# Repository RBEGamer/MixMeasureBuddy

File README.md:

# MixMeasureBuddy

MixMeasureBuddy's smart cocktail scale revolutionizes home bartending by offering accurate ingredient measurements and a vast library of cocktail recipes personalized to your liquor collection. Enjoy the art of mixology with ease and precision.

Discover the advanced features that set MixMeasureBuddy apart from traditional kitchen scales.

## FEATURES

Discover the advanced features that set MixMeasureBuddy apart from traditional kitchen scales:

* **Open-Source** MixMeasureBuddy is 100% open-source and can be build using a few simple and cheap parts.
* **Connectivity Features** Enjoy seamless integration with a companion webapp for sharing personalized cocktail recipes with other MixMeasureBuddy owners.
* **Offline Usage** Recipes are stored offline and locally on the MixMeasureBerry and can be edited using a text editor
* **User-Friendly Interface** Easily navigate the scale's intuitive interface for effortless cocktail making.
* **Customizable Recipes** Access a plethora of cocktail recipes tailored to your liquor cabinet for endless mixing possibilities.
* **Precision Measurements** Eliminate the guesswork and achieve consistent results with exact ingredient measurements every time.

## BOM

### 3D PRINTED PARTS

**Please read the 3d printing instructions before printing any part!**

* 1x `ring.stl`
* 1x `breadboard_mount.stl`
* 1x `inner_cellplate.stl`
* 1x `hinge.stl`
* 1x `bottom.stl`
* 1x `display_clamp.stl`
* 1x `display_mount.stl`
* 1x `encoder_clamp.stl`

#### CELLPLATE

* 1x `cellplate_<style>.stl`

The top plate exists in three different styles:

* `normal` - plain top plate
* `ring` - with an 82-84mm diameter ring depression in the center to plate a rubber band in it
* `plate` - with an 80mm diameter circular depression to place a rubber sheet in it

The `ring` and `plate` variants offer better grip of the glasses while standing on the platic top plate.

#### BOTTOM PLATE

If a `8mm` wide led strip is used please set the scale of `bottom.stl` to `120%` in **Z** direction.

#### 3D PRINT SETTINGS

* Layer height: `0.2` - `0.4`mm
* Support: `Support on buildplate only`
* Inflill: `20%`

### MECHANICAL

* 6x `Heat Inserts M3`
* 6x `M3x10 BHCS`
* 4x `M4x10 BHCS` - depends on load cell screw threads
* 3x `Heat Inserts M4`
* 3x `M4x10 BHCS`
* 8x `Cylindrical Magnet D5mm H8mm` or four additional `Heat Inserts M4` + four additional `M4x10 SHCS` to replace the magnets

### MISC

* `Super Glue` - to glue magnets into `inner_cellplate` and `cellplate`

### ELECTRICAL

* 1x `Raspberry Pi Pico` or `Raspberry Pi Pico W`
* 1x `LOAD CELL` with dimensions of `60x12x12mm` and at least `2kg`, for example `YZC-131`
* 1x `HX711`
* 1x `1.3" I2C OLED SSH1306`
* 1x `Encoder` e.g. `KY-040`
* 50cm `WS2812` strip
* Jumperwires  >12x `male-male`, >10x `male-female`
* 1x Breadboard with dimensions of `83 x 55mm`, for example `Mini Breadboard 400 Pin`
* [OPTIONAL] `SPI SD TF Karte Memory Card Shield Modul`
* [OPTIONAL] `Battery Expansion Shield 18650 V3`

### TOOLS

* `Soldering Iron`
* `Hotglue`

## HARDWARE BUILD

### SCHEMATIC

The following diagram shows the internal wiring of the individual components of the `MixMeasureBuddy`.
Only the `Raspberry Pi Pico`, button and the `HX711` are placed on the small breadboard.
The display, `LEDs` and the encoder(-module) are connected with longer cables so that they can be attached to the 3D printed parts at the intended mounting locations.

The circuit diagram was created in the Fritzing software. The project can be found under `documenation/schematic/`.
After the function of all parts has been tested, the connections on the breadboard should be fixed with hot glue so that they do not come loose during transportation.

### NOTES

To fix accuracy issues on several `HX711` boards, two addional resistors are needed.
Please refer to this guide: [HX711 – Auswahl und Beschaltung](https://beelogger.de/sensoren/waegezellen_hx711/hx711_beschaltung/#:~:text=HX711%20Modul%20Auswahl,Wägezelle%20und%20einen%20einstellbaren%20Messbrückenverstärker.)

#### [OPTIONAL] SD CARD READER

It is possible to connect an additional SD card reader. This makes it possible to save the recipes on an SD card.  
Please connect the SD card reader to the following pins on the `Raspberry Pi Pico`:

| Raspberry Pi Pico GPIO | SD CARD MODULE GPIO |
|------------------------|---------------------|
| VCC (Pin 36)           | 3V3 (OUT) / VCC     |
| GND (Pin 18)           | GND                 |
| GP10                   | SCK                 |
| GP8                    | MISO                |
| GP11                   | MOSI                |
| GP9                    | CS                  |

No further software changes are needed later on. The systems firmware detects the connected SD card automatically.

#### [OPTIONAL] BATTERY EXPANSION

The `Battery Expansion Shield 18650 V3` can be mounted on the `breadboard_mount.stl` later on.
In oder to connect the `Battery Expansion` to the `Raspberry Pi Pico GPIO` please follow the wiring table below:

| Raspberry Pi Pico GPIO | Battery Expansion |
|------------------------|-------------------|
| VBUS (Pin 40)          | 5V OUT            |
| GND  (Pin 38)          | GND               |

## SOFTWARE INSTALLATION

Please check the `Releases` page of this repository for prebuild firmware archives.

To initially flash the software to the `Raspberry Pi Pico`, the `BOOT` button must first be held down when plugging in the `USB` cable.
A new removable disk will then appear on the `PC`. The `firmware.uf2` is then copied to this.
The microcontroller will then restart and the MixMeasureBuddy logo should appear on the display.

If you want to build the software yourself from source or add modifications, please refer to the `SOFTWARE DEVELOPMENT` chapter.

**NOTE** There is an firmware archive with older stable versions located in `src/firmware/build/archive`.

### SOFTWARE UPGRADE

If a old version of the firmwre was already installed on the `Raspberry Pi Pico`, please flash the [flash_nuke.uf2](https://github.com/dwelch67/raspberrypi-pico/blob/main/flash_nuke.uf2) first! This clears all user settings!

**NOTE** Please backup all your stored recipes first!

## MECHANICAL BUILD

### 1. DISPLAY MOUNT

* 1x `Heat Inserts M3`
* 1x `M3x10`
* 1x `1.3" I2C OLED SSH1306`
* 4x Jumperwires `male-female`
* 1x `display_clamp.stl`
* 1x `display_mount.stl`

#### INSTRUCTIONS

1. Insert the `M3 Heat Insert` using a soldering iron into `display_mount`
2. Place the `1.3" I2C OLED SSH1306` display inside `display_mount` 
3. Press the display into place using the `display_clamp` and one `M3x10`
4. Connect four `male-female` jumperwires onto the display header
5. Glue the jumperwire ends and the header together using a drop of hotgleue
6. [OPTIONAL] Lock down the jumperwires using a small zip-tie

### 2. ENCODER MOUNT

* 2x `Heat Inserts M3`
* 1x `M3x10`
* 4x Jumperwires `male-female`
* 1x `Encoder` e.g. `KY-040`
* 1x `encoder_clamp.stl`
* 1x `ring.stl`

#### INSTRUCTIONS

1. Connect five `male-female` jumperwires onto the encoder pcb header
2. Insert the two `M3 Heat Inserts` using a soldering iron into `ring` part
3. Insert the encoder pcb into `ring` shell
4. Use the `encoder_clamp` and one `M3x10` to press the encoder into the `ring`

### 3. ASSEMBLE DISPLAY AND RING PARTS

* 1x `M3x10`
* 1x `hinge.stl`

#### INSTRUCTIONS

* Place the display assembly in the indentation
* Use the `hinge` and  one `M3x10` to press the assembly into the `ring`

### 3. LOADCELL

* 4x `M4x10` - depends on load cell screw threads
* 4x `Cylindrical Magnet D5mm H8mm`
* 1x `LOAD CELL`

* 1x `inner_cellplate.stl`

#### INSTRUCTIONS

1. Insert the three `M4 Heat Inserts` using a soldering iron into `ring` part
2. Screw the loadcell using two `M4x10` screws into the `ring`
3. Use the remaining `M4x10` screws to mount the `inner_cellplate` on the load cell arm, in the center of the `ring` cutout
4. Glue four magnets into `inner_cellplate`

**NOTE** The cables from the load cell are facing towards the shell of the `ring`

### 4. BREADBOARD

* 4x `Heat Inserts M3`
* 4x `M3x10 BHCS`
* 1x `ASSEMBLED BREADBOARD`
* 1x `breadboard_mount.stl`

#### INSTRUCTIONS

1. Insert the four `M3 Heat Inserts` using a soldering iron into `breadboard_mount` part
2. [OPTIONAL] Screw the `Battery Expansion Shield 18650 V3` into the side using two `M3x10`
3. Remove the protective film from the breadboard bottom side and place it ontop `breadboard_mount`stl`
4. Use the remaining two `M3x10` screws to fix `breadboard_mount` and `ring` together into place

**NOTE** Please connect all remaining components (`Encoder`, `Display`, ...) to the breadboard. See chapter `SCHEMATIC` again.
**NOTE** Its a good time to test the electronics again! Please refer to the `SOFTWARE INSTALLATION` chapter.

### 5. BOTTOM

* `WS2812` strip
* 3x `M4x10 SHCS`
* 3x  Jumperwire `male-male`
* 1x `bottom.stl`

#### INSTRUCTIONS

1. Solder three `male-male` jumperwires onto the `WS2812` strip (`VCC`, `GND`, `DIN`)
2. Remove the protective film from the `WS2812` strip and place them on the center ring of the `bottom`
3. Screw the `bottom` using the three `M4x10` screws onto `ring` assembly.

**NOTE** Make sure that the `Micro USB` is going thought opening between `bottom`  and `ring`.
**NOTE** If no `Battery Expansion Shield 18650 V3` is installed, please insert a `Micro USB` cable into the `Raspberry Pi Pico` before attaching the `bottom`.

### 6. CELLPLATE

* 4x `Cylindrical Magnet D5mm H8mm` or 4x `M4x6.x mm` heat inserts + 4x `M4x10 SHCS` to replace the magnets
* 1x `cellplate.stl`

#### INSTRUCTIONS

##### USING MAGNETS
1. Glue four magnets into `cellplate`
2. Place the `cellplate` on the `inner_cellplate`

**NOTE** Please ensure that the magnets in the two parts `cellplate`, `inner_cellplate` attract each other on opposite sides

##### USING HEAT INSERTS

1. Insert the `heatinserts` in the four holes of the `cellplate`
2. 
3. Place the `cellplate` on the `inner_cellplate`
4. Align the flat edge of the `cellplate` with the display and use the four `M4x10 SHCS` screws to connect the `cellplate` with `inner_cellplate`

# USAGE

Once the hardware has been set up and the software has been flashed to the microcontroller, the system can be set up for the first time.
The basic operation and calibration of the system is described below.

## MENU NAVIGATION

After switching on the power supply, e.g. via a power bank, the main menu appears on the display immediately after the logo screen.
Navigation in the system is very easy thanks to the rotary encoder. 
The right and left rotation of the encoder can be used to scroll through the separate menu entries.
If you want to enter / activate a menu item, simply press the button on the encoder.
To exit a menu/recipe, the encoder button must be held down for at least half a second.

## CALIBRATION

If the scales menu or a recipe is now called up. The weighing results can deviate significantly from reality.
This is due to the installation direction of the load cell, its mounting and other factors.
The menu item `CALIBRATION` is provided for this purpose.
For this process, the scale is measured with and without weight and the corresponding correction factors are determined.

A known weight with at least `50g` is therefore required. This can be a glass of water, for example, which has previously been measured with a kitchen scale.

After starting the calibration routine, the user is guided through the following steps one after the other:

* Measure empty scale
* User enters weight of calibration object
* User places calibration object on scale
* User removes calibration object if shown by display

**NOTE** If the scales light up red, please `DONT MOVE OR TOUCH`.

**NOTE** The `IKEA POKAL` glass has a weight of 390g (empty) :)

## RUN A RECIPE

## ADDING CUSTOM RECIPES

A recipe in the context of the MixMeasureBuddy consists of a JSON object in a .recipe file. This contains meta data such as the name and description of the recipe as well as a series of instructions that the user should execute to complete the recipe. The following instruction types can be used for this purpose:

* SCALE - Weigh until x grams reached
* WAIT - Wait x seconds
* CONFIRM - Confirm that it has been done.

There are two ways to create a new recipe manually:

### BY USING recipe.py CLASS

* Create a new empty folder
* Copy the `src/firmware/src/static_modules/recipe.py` into the new created folder
* Create a new `MyRecipe.py` file with the following content Python script below
* Change the name, description and steps according your imagination

```python
# SEE example_recipes.py FOR FURTHER / DETAILED EXAMPLES
import recipe

example_recipe: recipe.recipe = recipe.recipe("Tequila Sunrise", "A nice Tequila Sunrise Cocktail", "1.0.0", ["Tequila"])
# ADD A SCALE STEP: ADD x g TO THE GLASS
example_recipe.add_step(recipe.recipe_step.create_scale_step(_ingredient_name="White Tequila", _target_value = 10))
# ADD A SCALE STEP: ADD x g TO THE GLASS
example_recipe.add_step(recipe.create_scale_step(_ingredient_name="Orange Juice", _target_value = 120))
# ADD CONFIRM STEP: ADD ICE AND CONFIRM WITH A BUTTON PRESS
example_recipe.add_step(recipe.create_scale_step(_ingredient_name="Ice", _current_step_text="Add Ice"))
# ADD A SCALE STEP: ADD x g TO THE GLASS
example_recipe.add_step(recipe.create_scale_step(_ingredient_name="Grenadine", _target_value = 40))
# ADD A WAIT STEP:  WAIT x SECONDS
example_recipe.add_step(recipe.create_scale_step(_current_step_text="Wait for settle down", _target_value = 10))

# EXPORT THE RECIPES AS JSON BASE .RECIPE FILE
with open("MyRecipe.recipe, "w") as file:
  file.write(json.dumps(example_recipe.to_dict()))
# COPY OVER THE .RECIPE FILE TO THE SCALE
```

Run the 

```bash
$ python MyRecipe.py
$ cat MyRecipe.recipe
```

This scripts created a new `MyRecipe.recipe` file. The content is a `JSON` strucutre which is compatible with the recipe system of the scale.

### CREATEING A JSON BASED .recipe FILE

```json
{
    "filename": "Tequila_Sunrise.recipe",
    "name": "Tequila Sunrise",
    "steps": [{
        "text": "",
        "ingredient": "White Tequila",
        "amount": 10,
        "action": 0
    }, {
        "text": "",
        "ingredient": "Orange Juice",
        "amount": 120,
        "action": 0
    }, {
        "text": "Add Ice",
        "ingredient": "Ice",
        "amount": -1,
        "action": 1
    }, {
        "text": "",
        "ingredient": "Grenadine",
        "amount": 40,
        "action": 0
    }, {
        "text": "Wait for settle down",
        "ingredient": "",
        "amount": 10,
        "action": 2
    }],
    "description": "A nice Tequila Sunrise Cocktail",
    "version": "1.0.0"
}
```

### COPY RECIPES TO SCALE

To access the files and the Micropython environment on the scale directly, its possible to use these two example programs below:

* [Thonny](https://github.com/thonny/thonny/)
* [rshell](https://github.com/dhylands/rshell)

In this example, a previously created recipe file is to be copied to the `MixMeasureBuddy` so that it can be used.
After connecting the flashed `MixMeasureBuddy` to a host PC using a USB cable, run the following commands in order to transfer the `.recipe` file.

#### THONNY

For installation, please refer to the installation guid on the website [INSTALL_THONNY](https://thonny.org).

The image shows the steps in order to connect the `MixMeasureBuddy` and access its files:

1. Select the board
2. Connect to python repl running on the board
3. Use the file explorer to add/edit/remove files 

#### RSHELL

```bash
# INSTALL RSHELL
$ sudo pip3 install rshell

#TEST CONNECTION
$ rshell
# OR
$ rshell -p /dev/ttyUSB0
# COPY
$ rshell cp MyRecipe.recipe /data/MyRecipe.recipe
```

The recipe is now stored on the `MixMeasureBuddy`. Powercycle the device to load the new recipes!

### USER CONFIGURATION

If a `Raspberry Pi Pico W` is used, its possible to use the recipe editor and the recipe api update functions.
Here the wifi credentials needs to be set using the `SETTINGS.json` file on the scale.
Please use the same procedure described above to edit files on the scale filesystem.

# FIRMWARE DEVELOPMENT

The microcontroller firmware of the `Raspberry Pi Pico` was created in micropython and is automatically created with the pre-built image. 
The source code files are located in the folder `src/firmware_rp2040` and the Python source code files in the folder `src/firmware_rp2040/src`.
The program `Thonny` can be used to adapt the software directly on the scale.

## DIFFERENT HARDWARE CONFIG

The global hardware configuration (used display type, pin definitions and other settings) are stored in the `Config.py` loacted in the virtual filesystem.
Its possbile to modify this file using the `REPL` or` Thonny` as described above.

## STRUCTURE

The entry point of the software is in the `main.py`, which is called by the custom pre-boot script `boot.py`. The general configuration of the hardware (e.g. which pins the buttons are connected to) is done in the `config.py` file.

The control of the hardware components is done in the files:

* `ui.py` - UI system + display control
* `ledring.py` - LED effects for the LED ring
* `Scales.py` - readout of the HX711
* `settings.py`- filesystem access for writing/reading recipe files and settings

All these classes can be easily called from all other scripts using the singleton pattern. This makes integration very simple and uniform:

```python
import ledring
import ui
import Scale
# CLEAR DISPLAY
ui().clear()
# SET LED RING
ledring().set_neopixel_full_hsv(ledring().COLOR_PRESET_HSV_H__BLUE)
# GET CURRENT SCALE MEASUREMENT
ScaleInterface().get_current_weight()
```

The individual menus are designed as a plug-in system. This allows you to quickly create your own extensions.
The plugins are designated in the system with the prefix `menu_entry_*.py` and the functions are derived from the base class `menu_entry.py`.
This consists of an `activate`, `teardown` and `update` function, which are called accordingly when the corresponding menu entry is called.

```python
class menu_entry_MyPlugin(menu_entry.menu_entry):

    def __init__(self):
        super().__init__("MyPlugin", "My nice plugin")
    # WILL BE CALLED IF USER SELECTS PLUGIN
    def preview(self):
        print("preview {}".format(self.name))
        ui().show_recipe_information(self.name, self.description)
    
    # WILL BE CALLED IF USER ACTIVATES PLUGIN
    # E.G. DO SETUP STUFF
    def activate(self):
        print("activate {}".format(self.name))
        ui().show_titlescreen()

    # WILL BE CALLED IF USER EXISTS PLUGIN
    # E.G. DELETE RESOURCES
    def teardown(self):
        print("teardown {}".format(self.name))

    # WILL BE CALLED IF A USER PRESSES A BUTTON, EVERY SECOND OR IF THE WEIGHT ON LOAD CELL CHANGES
    def update(self, _system_command: system_command.system_command):
        
        if _system_command.type == system_command.system_command.COMMAND_TYPE_NAVIGATION:
            if _system_command.action == system_command.system_command.NAVIGATION_ENTER: #  OK BUTTON
                pass
            elif _system_command.action == system_command.system_command.NAVIGATION_LEFT: # NEXT BUTTON
                pass
            elif _system_command.action == system_command.system_command.NAVIGATION_RIGHT: # PREV BUTTON
                pass

        elif _system_command.type == system_command.system_command.COMMAND_TYPE_SCALE:
              print("CURRENT WEIGHT: {}".format(_system_command.value))
  
        elif _system_command.type == system_command.system_command.COMMAND_TYPE_TIMER_IRQ:
              print("ELAPSED TIME SINCE LAST CALL: {}".format(_system_command.value))
           
```

To add the plugin, import the module in `main.py` and add the class into the menu tree:

```python
from menu_entry_MyPlugin import menu_entry_MyPlugin
menu_manager.menu_manager().add_subentries(menu_entry_MyPlugin.menu_entry_MyPlugin())
```

Its also possible to add sub-menus using the `menu_entry_submenu` plugin:

```python
# CREATE SUBMENU WITH CUSTOM TITLE
submenu: menu_entry_submenu.menu_entry_submenu = menu_entry_submenu.menu_entry_submenu("SYSTEM", "ACCESS SYSTEM SETTINGS")
# ADD MENU ENTRIES TO THE SUBMENU
submenu.add_subentries(menu_entry_calibration.menu_entry_calibration())
submenu.add_subentries(menu_entry_calibration.menu_entry_calibration())
submenu.add_subentries(menu_entry_calibration.menu_entry_calibration())
# ADD THE SUBMENU TO THE MAIN MENU
menu_manager.menu_manager().add_subentries(submenu)
```

## FIRMWARE IMAGE

To create a finished and complete firmware image, the folder `src/firmware_rp2040` contains a bash script which creates the images using `Docker` for the `Raspberry Pi Pico` and `Raspberry Pi Pico W` and the required boot configurations.

```bash
# INSTALL AND RUN DOCKER https://docs.docker.com/engine/install/
$ cd src/firmware_rp2040
$ bash ./build_firmware_docker.sh
# RESULTS ARE LOCATED IN THE build FOLDER
```

## BUILD SYSTEM BACKGROUND

One problem was how to build and distribute the Micropython images automatically via e.g. GitHub.
The way documented by Micropython does not allow the user to change the code and data after building the u2f, because they are permanently written to the flash (static/lib) fodlers.
That's why the complicated build process was created using a Docker image that installs a pre application boot procedure, so that the user source code to the Python file system during the first boot.
This way, functions can be easily added/modified by the user and at the same time the finished software can be easily distributed.

# TODO

* Cocktail database webapp - `src/webapp`

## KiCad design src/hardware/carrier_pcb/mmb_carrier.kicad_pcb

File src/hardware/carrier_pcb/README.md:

# MixMeasureBuddy carrier PCB (Raspberry Pi Pico 2 W)

A 2-layer, 83 × 70 mm board that replaces the breadboard and jumper-wire nest. The top 83 × 55 mm is the breadboard-sized area; the bottom 15 mm band holds the optional LiPo section.

* **Raspberry Pi Pico 2 W**: socketed on 2 × 20 pin headers (or soldered directly), with USB at the board edge
* **HX711** load-cell ADC (v1.1): a ready-made HX711 module plugs into the J4 socket (the bare chip circuit of v1.0 was removed)
* **2 navigation buttons** (LEFT / RIGHT): 6 × 6 mm THT tactile switches on the board
* Headers for the **OLED**, **encoder**, **WS2812 ring**, **load cell**, optional **SD card** and optional **5 V battery shield**
* **Optional LiPo section**: charger, step-up converter, power switch header and battery-voltage sense
* **Stepper driver socket** (v1.1): a StepStick / Pololu-footprint socket (A4988, DRV8825, TMC2208/2209 modules) with a 4-pin motor header
* **USB-C PD motor supply** (v1.1): a second USB-C port with a CH224K PD trigger that asks the charger for **12 V** for the motor only

KiCad 10 project: `mmb_carrier/` (`.kicad_pro`, `.kicad_sch`, `.kicad_pcb`).
Status: ERC 0 violations, DRC 0 violations, 0 unconnected items, 0 schematic-parity issues.

| Top | Bottom |
|---|---|
|  |  |

## Pin mapping (matches `src/firmware/src/config.py`, so the firmware works unchanged)

| Function | Pico GPIO (pin) | Board connector |
|---|---|---|
| OLED SDA / SCL (I2C0) | GP16 (21) / GP17 (22) | J1: 1 GND, 2 VCC (3V3), 3 SCL, 4 SDA |
| Encoder CLK / DT / SW | GP20 (26) / GP19 (25) / GP18 (24) | J2: 1 CLK, 2 DT, 3 SW, 4 + (3V3), 5 GND, in KY-040 order |
| WS2812 data | GP28 (34), through 330 Ω R3 | J3: 1 +5V (VSYS), 2 DIN, 3 GND |
| Button LEFT / RIGHT | GP3 (5) / GP2 (4), switch to GND (internal pull-up) | SW1 / SW2 |
| HX711 module SCK / DT | GP4 (6) / GP5 (7) | J4 socket: 1 GND, 2 DT, 3 SCK, 4 VCC (3V3) |
| Load cell | n/a | soldered to the HX711 module: E+ red, E- black, A- white, A+ green |
| SD card (SPI1, optional) | GP8 MISO, GP9 CS, GP10 SCK, GP11 MOSI | J5: 1 GND, 2 3V3, 3 MISO, 4 MOSI, 5 SCK, 6 CS |
| 5 V in (battery shield, optional) | VBUS (40) | J6: 1 +5V, 2 GND |
| LiPo cell (optional) | n/a | J7 JST-PH 2.0: 1 = **+**, 2 = − |
| Power switch (optional) | n/a | J8: external on/off switch, or a jumper for always-on |
| Battery voltage (optional) | GP26 / ADC0 (31) = VBAT / 2 | n/a |
| Stepper STEP / DIR | GP6 (9) / GP7 (10) | A1 StepStick socket |
| Stepper EN (active low) | GP1 (2), 10k pull-up R13 = driver off at boot | A1 StepStick socket |
| Stepper motor | n/a | J10: 1 = 1B, 2 = 1A (coil 1), 3 = 2A, 4 = 2B (coil 2); silk shows 2B 2A 1A 1B from left to right |
| Motor supply 12 V | n/a | J9 USB-C (power only), PD charger required |

## Optional LiPo section (bottom band)

Leave every part in the band unpopulated if you don't need a battery; the rest of the board works the same without it.

* **Charger, U3 (MCP73831-2-OT):** charges a single 3.7 V LiPo from USB at 500 mA (R4 = 2 kΩ; use 4.7 kΩ for about 200 mA with small cells). The red CHG LED is on while the cell is charging.
* **Load sharing (Q2 AO3401A + D1):** with USB plugged in, the step-up runs from USB and the battery only charges. Without USB, Q2 connects the battery.
* **Power switch, J8:** sits in series with the step-up input. Wire a slide switch from the enclosure to it, or fit a jumper. The battery still charges while the switch is off.
* **Step-up, U4 (MT3608):** makes 5.1 V with a 10 µH inductor and R7/R8 = 75k/10k. D3 feeds that into VSYS, the Pico's recommended way to add a second power source. The WS2812 header now runs from VSYS, so the ring works on battery too. The MT3608 handles roughly 0.8–1 A out of a LiPo, which is plenty for the 26 LEDs at the firmware's brightness limit.
* **Battery level:** R9/R10 (220k/220k) put VBAT/2 on GP26. The current firmware doesn't read it yet; in MicroPython, `machine.ADC(26).read_u16() * 3.3 / 65535 * 2` gives the battery voltage.
* **⚠ Check polarity:** JST-PH LiPo leads are not standardized. Before plugging in a cell, make sure its red wire lands on pin 1 (marked **+**).

## Stepper driver and 12 V USB-C PD supply (v1.1)

* **Driver socket, A1:** two 1 × 8 female 2.54 mm headers, 12.7 mm (0.5") apart, for any StepStick-pinout module. The silkscreen inside the socket marks **GND / DIR** at the top (Pico side) and **VMOT / EN** at the bottom. The square pad is GND. Check the orientation before plugging in a module: a reversed driver is destroyed as soon as power is applied.
* **Logic:** VDD = 3V3, so STEP / DIR / EN use 3.3 V logic. EN has a 10k pull-up (R13), so the motor stays de-energised until the firmware drives GP1 low. RESET and SLEEP are tied together and pulled high (R14).
* **Microstepping:** JP1 / JP2 / JP3 (labelled MS1 / MS2 / MS3) are open solder jumpers. Open = low, bridged = 3V3. The resulting mode depends on the module (A4988 / DRV8825: all open = full step; TMC2209: MS1 = MS2 = low = 1/8 step). On some TMC220x modules the MS3 / RESET positions carry PDN/UART instead, so check the module's pinout.
* **Motor supply, J9 + U5 (CH224K):** a USB-C power-only receptacle feeds **VMOT only**; the Pico, LEDs and HX711 keep running from the Pico's own USB (or the LiPo section). CH224K negotiates 12 V with R12 = 24k (6.8k = 9 V, 56k = 15 V). It is PD only: DP/DM are shorted on the chip side and not wired to the receptacle. VDD is fed from VBUS through R11 (1k) with C12 (1 µF).
* **Bulk capacitance:** C14 100 µF / 25 V low-ESR electrolytic plus C13 100 nF, next to the VMOT pin. If you change R12 to 15 V, keep the 25 V cap. For 20 V (R12 not fitted) use a 35 V part.
* **Charger requirement:** the charger must offer a 12 V PD profile (check its label). Some chargers only offer 5/9/15/20 V, and with those VMOT stays at 5 V. A4988 / DRV8825 drivers stay in under-voltage lockout at 5 V, while TMC2209 modules run (weakly) from 5 V.
* **Layout:** the whole motor power loop (USB-C, bulk cap, driver, motor header) sits in the left half of the board, far from the HX711 module socket J4 on the right edge. VMOT is routed at 0.8 mm and the motor phases at 0.6 mm, both without vias.
* **Moved for v1.1:** SW1 / SW2 (LEFT / RIGHT) moved to the right of the driver socket, and the SD header J5 moved 2.54 mm to the right. Nets and pin mapping are unchanged.
* **Firmware:** not changed yet; the pins above (GP6 STEP, GP7 DIR, GP1 EN) are free in `config.py`.

## HX711 module (v1.1)

* **J4** is a 1 × 4 female 2.54 mm socket on the right board edge. A ready-made HX711 module (the common green or red board) plugs in with its 4-pin header. The pin order is **GND, DT, SCK, VCC**, as printed on most modules and next to J4 on the silkscreen. If your module uses a different order, wire it to the labels instead of plugging it in directly.
* The module is powered from **3V3**, so DT and SCK use 3.3 V logic and are safe for the RP2350. The area next to J4 (where the v1.0 HX711 chip sat) is free of parts, so the module can lie flat there on right-angle pins, or stand upright in the socket.
* Solder the load cell to the module's E+ / E- / A- / A+ pads (red, black, white, green on most cells).
* GP4 (SCK) and GP5 (DT) are the same pins as before, so the firmware works unchanged. The bare-chip circuit (U2, Q1, R1, R2, C1-C6) and the old load-cell header are gone.
* Many cheap modules need the accuracy fix described in the main README's HX711 note (the linked beelogger guide). Apply it on the module itself.
* After swapping the excitation source (module instead of the v1.0 on-board circuit), run the calibration menu once.

## Layout notes

* The Pico W/2 W antenna keepout from the footprint is respected: no copper or tracks under the antenna end.
* Both layers have a GND pour with stitching vias on a 5 mm grid.
* Four M3 mounting holes sit at 4 mm from each corner.
* Reference designators in the LiPo band and in the USB-C PD / stepper area (except A1 and J10) are on the fab layer only (no space for silkscreen); see the schematic or the pick-and-place file.
* Signal tracks are 0.25 mm, supply tracks 0.4–0.5 mm, VMOT 0.8 mm and motor phases 0.6 mm, with 0.2 mm clearance and 0.6/0.3 mm vias. Any standard 2-layer fab can make this.

## Fabrication files (`mmb_carrier/fab/`)

* `mmb_carrier_gerbers.zip`: Gerbers and Excellon drill file
* `mmb_carrier_bom.csv`: BOM with an `LCSC` column (plus 2 × 1×20 female 2.54 mm headers if you socket the Pico, and 2 × 1×8 female 2.54 mm headers for the A1 stepper socket)
* `mmb_carrier_pos.csv`: pick-and-place file for the SMD parts (KiCad format)
* `mmb_carrier_jlcpcb_bom.csv` + `mmb_carrier_jlcpcb_cpl.csv`: BOM (`Comment, Designator, Footprint, LCSC`) and placement file (`Designator, Mid X, Mid Y, Layer, Rotation`) for JLCPCB SMT assembly of the 30 SMD parts

### LCSC part numbers

Every orderable part carries an `LCSC` field in the schematic and on the PCB footprint. The numbers were checked against the LCSC / JLCPCB part pages (November 2026); check stock before ordering.

| Part | LCSC | Notes |
|---|---|---|
| 0805 resistors 330 / 1k / 2k / 10k / 24k / 75k / 100k / 220k | C17630 / C17513 / C17604 / C17414 / C17575 / C17819 / C149504 / C17556 | UNI-ROYAL 0805W8F series, 1 %; 75k is an extended part |
| 100 nF 0805 / 1 µF 0805 / 4.7 µF 0805 / 22 µF 1206 | C49678 / C28323 / C1779 / C12891 | X7R 50 V, X7R 50 V, X5R 25 V, X5R 25 V |
| C14 100 µF 25 V, 6.3 × 5.8 mm | C178540 | Panasonic EEE-FK1E101SP |
| SS14 / red 0805 LED / AO3401A | C2480 / C84256 / C15127 | |
| MCP73831T-2ACI/OT / MT3608 / CH224K | C424093 / C84817 / C970725 | extended parts |
| L1 Bourns SRN6045TA-100M | C2046332 | second source on the same footprint: SXN SMNR6045-100MT, C135304 |
| J9 GCT USB4125-GF-A (USB-C, power only) | C3151650 | exact part for the footprint |
| J4 1×4 female header / A1 1×8 female header (2 pcs) | C2718488 / C27438 | 8.5 mm high |
| J7 JST S2B-PH-K-S / SW1, SW2 6 × 6 × 5 mm tact switch | C173752 / C393938 | |
| Male pin headers J1-J3, J5, J6, J8, J10 | C2337 | 1×40 breakable, cut to length (no field on the symbols) |

The JLCPCB files cover the SMD parts only; the through-hole parts (headers, switches, JST, Pico) are hand-soldered. Rotations in the CPL are KiCad's: check the part orientation in JLCPCB's placement preview before confirming, especially for the SOT-23 parts, the diodes, the electrolytic C14, U5 and J9.
* `../mmb_carrier_schematic.pdf`: schematic

## Regenerating

The board is generated from `tools/design.py`, which holds the parts, pins and nets. To rebuild:

```bash
tools/build.sh
```

The script writes the schematic, runs ERC, places parts, routes the board with the bundled grid router (`tools/gen_pcb.py`), pours GND, runs DRC with schematic parity, and exports the fab outputs. If you edit the board by hand in KiCad, stop using the script for that board, because the next run overwrites it.

**Note for v1.1:** the stepper / USB-C PD rework was added directly to the KiCad files, not to `tools/design.py`. Running the old generator would remove it.

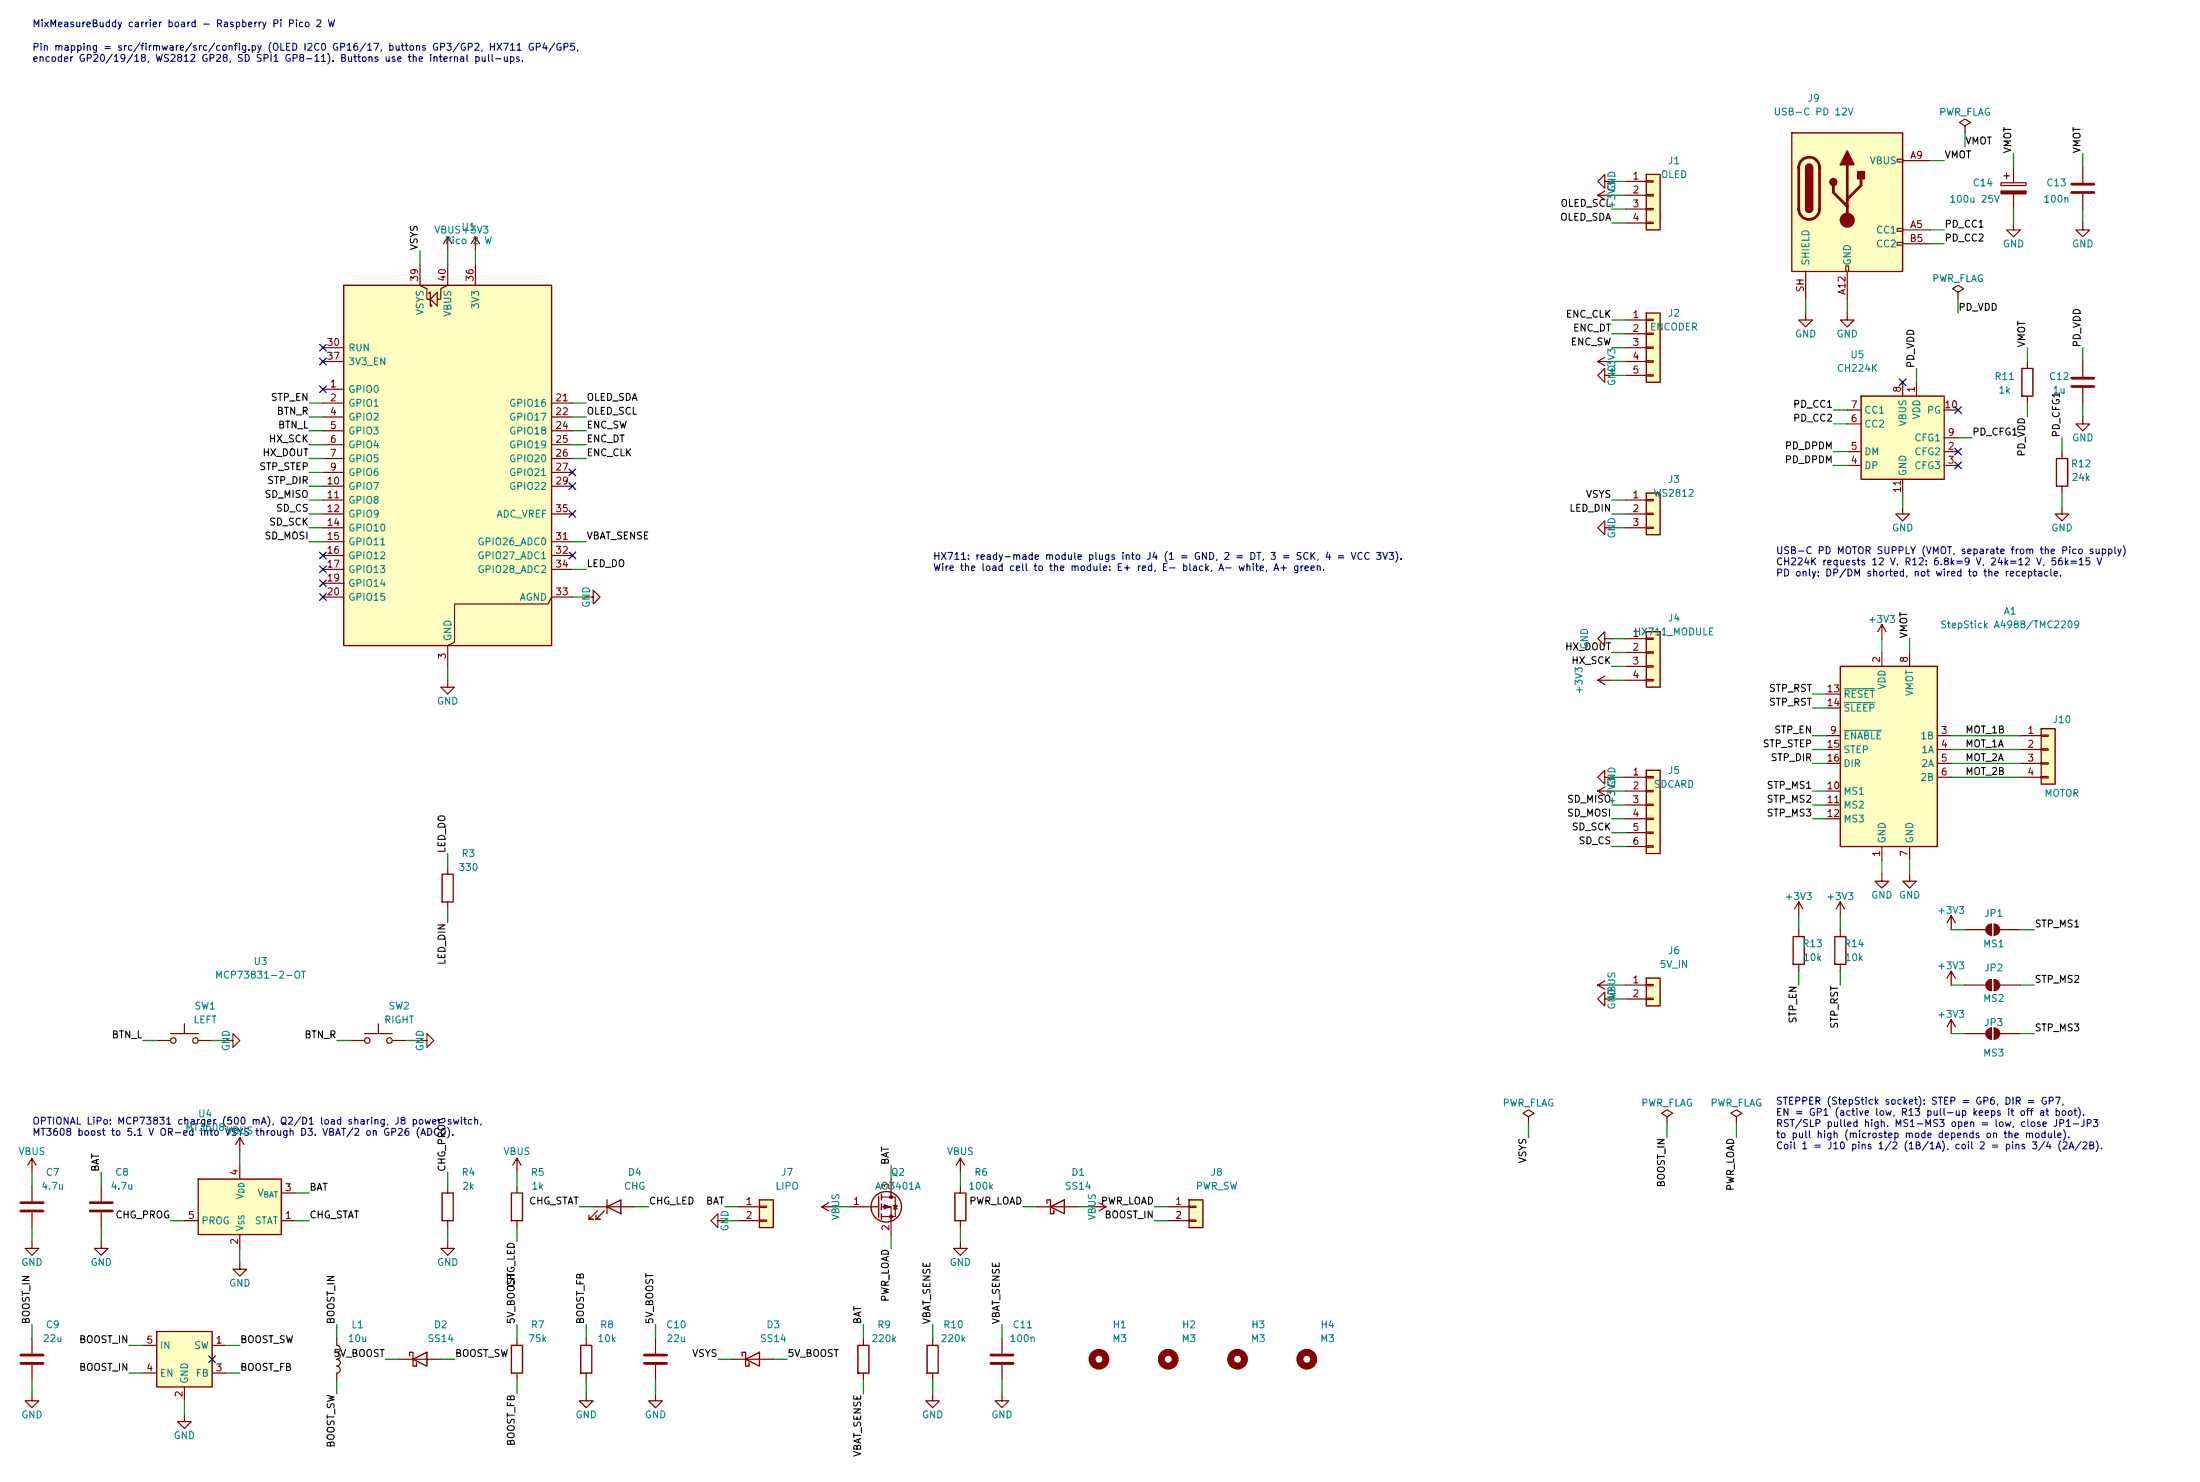
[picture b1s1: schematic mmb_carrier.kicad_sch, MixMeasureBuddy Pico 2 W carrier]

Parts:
A1: StepStick A4988/TMC2209; Pololu_Breakout-16_15.2x20.3mm; LCSC C27438
C7, C8: 4.7u; C_0805_2012Metric; LCSC C1779
C9, C10: 22u; C_1206_3216Metric; LCSC C12891
C11, C13: 100n; C_0805_2012Metric; LCSC C49678
C12: 1u; C_0805_2012Metric; LCSC C28323
C14: 100u 25V; CP_Elec_6.3x5.8; LCSC C178540
D1, D2, D3: SS14; D_SMA; LCSC C2480
D4: CHG; LED_0805_2012Metric; LCSC C84256
H1, H2, H3, H4: M3; MountingHole_3.2mm_M3
J1: OLED; PinHeader_1x04_P2.54mm_Vertical
J2: ENCODER; PinHeader_1x05_P2.54mm_Vertical
J3: WS2812; PinHeader_1x03_P2.54mm_Vertical
J4: HX711_MODULE; PinSocket_1x04_P2.54mm_Vertical; LCSC C2718488
J5: SDCARD; PinHeader_1x06_P2.54mm_Vertical
J6: 5V_IN; PinHeader_1x02_P2.54mm_Vertical
J7: LIPO; JST_PH_S2B-PH-K_1x02_P2.00mm_Horizontal; LCSC C173752
J8: PWR_SW; PinHeader_1x02_P2.54mm_Vertical
J9: USB-C PD 12V; USB_C_Receptacle_GCT_USB4125-xx-x_6P_TopMnt_Horizontal; LCSC C3151650
J10: MOTOR; PinHeader_1x04_P2.54mm_Vertical
JP1: MS1; SolderJumper-2_P1.3mm_Open_RoundedPad1.0x1.5mm
JP2: MS2; SolderJumper-2_P1.3mm_Open_RoundedPad1.0x1.5mm
JP3: MS3; SolderJumper-2_P1.3mm_Open_RoundedPad1.0x1.5mm
L1: 10u; L_Bourns_SRN6045TA; LCSC C2046332
Q2: AO3401A; SOT-23; LCSC C15127
R3: 330; R_0805_2012Metric; LCSC C17630
R4: 2k; R_0805_2012Metric; LCSC C17604
R5, R11: 1k; R_0805_2012Metric; LCSC C17513
R6: 100k; R_0805_2012Metric; LCSC C149504
R7: 75k; R_0805_2012Metric; LCSC C17819
R8, R13, R14: 10k; R_0805_2012Metric; LCSC C17414
R9, R10: 220k; R_0805_2012Metric; LCSC C17556
R12: 24k; R_0805_2012Metric; LCSC C17575
SW1: LEFT; SW_PUSH_6mm; LCSC C393938
SW2: RIGHT; SW_PUSH_6mm; LCSC C393938
U1: Pico 2 W; RaspberryPi_Pico_Common_THT
U3: MCP73831-2-OT; SOT-23-5; LCSC C424093
U4: MT3608; SOT-23-6; LCSC C84817
U5: CH224K; SSOP-10-1EP_3.9x4.9mm_P1mm_EP2.1x3.3mm; LCSC C970725

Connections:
+3V3: A1.2 (VDD), J1.2, J2.4, J4.4, J5.2, JP1.1 (A), JP2.1 (A), JP3.1 (A), R13.1, R14.1, U1.36 (3V3)
/5V_BOOST: C10.1, D2.1 (K), D3.2 (A), R7.1
/BAT: C8.1, J7.1, Q2.3 (D), R9.1, U3.3 (V_{BAT})
/BOOST_FB: R7.2, R8.1, U4.3 (FB)
/BOOST_IN: C9.1, J8.2, L1.1, U4.4 (EN), U4.5 (IN)
/BOOST_SW: D2.2 (A), L1.2, U4.1 (SW)
/BTN_L: SW1.1, U1.5 (GPIO3)
/BTN_R: SW2.1, U1.4 (GPIO2)
/CHG_LED: D4.2 (A), R5.2
/CHG_PROG: R4.1, U3.5 (PROG)
/CHG_STAT: D4.1 (K), U3.1 (STAT)
/ENC_CLK: J2.1, U1.26 (GPIO20)
/ENC_DT: J2.2, U1.25 (GPIO19)
/ENC_SW: J2.3, U1.24 (GPIO18)
/HX_DOUT: J4.2, U1.7 (GPIO5)
/HX_SCK: J4.3, U1.6 (GPIO4)
/LED_DIN: J3.2, R3.2
/LED_DO: R3.1, U1.34 (GPIO28_ADC2)
/MOT_1A: A1.4 (1A), J10.2
/MOT_1B: A1.3 (1B), J10.1
/MOT_2A: A1.5 (2A), J10.3
/MOT_2B: A1.6 (2B), J10.4
/OLED_SCL: J1.3, U1.22 (GPIO17)
/OLED_SDA: J1.4, U1.21 (GPIO16)
/PD_CC1: J9.A5 (CC1), U5.7 (CC1)
/PD_CC2: J9.B5 (CC2), U5.6 (CC2)
/PD_CFG1: R12.1, U5.9 (CFG1)
/PD_DPDM: U5.4 (DP), U5.5 (DM)
/PD_VDD: C12.1, R11.2, U5.1 (VDD)
/PWR_LOAD: D1.1 (K), J8.1, Q2.2 (S)
/SD_CS: J5.6, U1.12 (GPIO9)
/SD_MISO: J5.3, U1.11 (GPIO8)
/SD_MOSI: J5.4, U1.15 (GPIO11)
/SD_SCK: J5.5, U1.14 (GPIO10)
/STP_DIR: A1.16 (DIR), U1.10 (GPIO7)
/STP_EN: A1.9 (~ENABLE), R13.2, U1.2 (GPIO1)
/STP_MS1: A1.10 (MS1), JP1.2 (B)
/STP_MS2: A1.11 (MS2), JP2.2 (B)
/STP_MS3: A1.12 (MS3), JP3.2 (B)
/STP_RST: A1.13 (~RESET), A1.14 (~SLEEP), R14.2
/STP_STEP: A1.15 (STEP), U1.9 (GPIO6)
/VBAT_SENSE: C11.1, R9.2, R10.1, U1.31 (GPIO26_ADC0)
/VMOT: A1.8 (VMOT), C13.1, C14.1, J9.A9 (VBUS), J9.B9 (VBUS), R11.1
/VSYS: D3.1 (K), J3.1, U1.39 (VSYS)
GND: A1.1 (GND), A1.7 (GND), C7.2, C8.2, C9.2, C10.2, C11.2, C12.2, C13.2, C14.2, J1.1, J2.5, J3.3, J4.1, J5.1, J6.2, J7.2, J9.A12 (GND), J9.B12 (GND), J9.SH (SHIELD), R4.2, R6.2, R8.2, R10.2, R12.2, SW1.2, SW2.2, U1.3 (GND), U1.8 (GND), U1.13 (GND), U1.18 (GND), U1.23 (GND), U1.28 (GND), U1.33 (AGND), U1.38 (GND), U3.2 (V_{SS}), U4.2 (GND), U5.11 (GND)
VBUS: C7.1, D1.2 (A), J6.1, Q2.1 (G), R5.1, R6.1, U1.40 (VBUS), U3.4 (V_{DD})

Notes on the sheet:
MixMeasureBuddy carrier board - Raspberry Pi Pico 2 W
Pin mapping = src/firmware/src/config.py (OLED I2C0 GP16/17, buttons GP3/GP2, HX711 GP4/GP5, encoder GP20/19/18, WS2812 GP28, SD SPI1 GP8-11). Buttons use the internal pull-ups.
OPTIONAL LiPo: MCP73831 charger (500 mA), Q2/D1 load sharing, J8 power switch, MT3608 boost to 5.1 V OR-ed into VSYS through D3. VBAT/2 on GP26 (ADC0).
USB-C PD MOTOR SUPPLY (VMOT, separate from the Pico supply) CH224K requests 12 V. R12: 6.8k=9 V, 24k=12 V, 56k=15 V PD only: DP/DM shorted, not wired to the receptacle.
STEPPER (StepStick socket): STEP = GP6, DIR = GP7, EN = GP1 (active low, R13 pull-up keeps it off at boot). RST/SLP pulled high. MS1-MS3 open = low, close JP1-JP3 to pull high (microstep mode depends on the module). Coil 1 = J10 pins 1/2 (1B/1A), coil 2 = pins 3/4 (2A/2B).
HX711: ready-made module plugs into J4 (1 = GND, 2 = DT, 3 = SCK, 4 = VCC 3V3). Wire the load cell to the module: E+ red, E- black, A- white, A+ green.

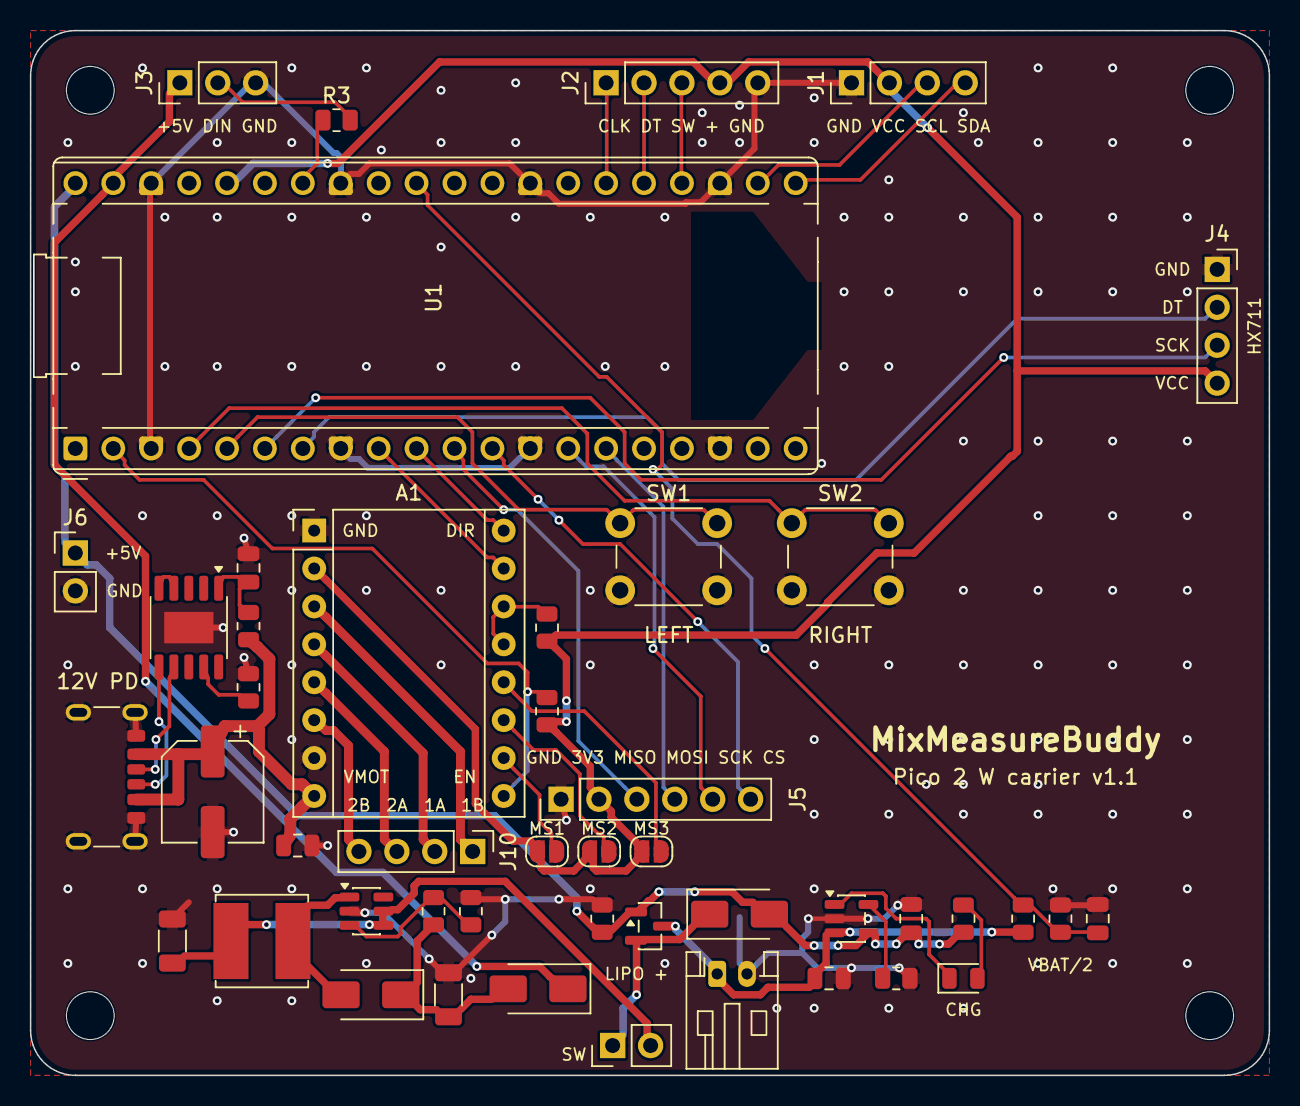
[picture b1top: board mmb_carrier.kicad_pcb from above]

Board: 2 copper layers, 83.0 x 70.0 mm, 50 parts (0 on the bottom side), 46 nets.

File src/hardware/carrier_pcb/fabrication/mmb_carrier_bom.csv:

"Reference","Value","Footprint","LCSC","QUANTITY"
"A1","StepStick A4988/TMC2209","Module:Pololu_Breakout-16_15.2x20.3mm","C27438","1"
"C7,C8","4.7u","Capacitor_SMD:C_0805_2012Metric","C1779","2"
"C9,C10","22u","Capacitor_SMD:C_1206_3216Metric","C12891","2"
"C11,C13","100n","Capacitor_SMD:C_0805_2012Metric","C49678","2"
"C12","1u","Capacitor_SMD:C_0805_2012Metric","C28323","1"
"C14","100u 25V","Capacitor_SMD:CP_Elec_6.3x5.8","C178540","1"
"D1-D3","SS14","Diode_SMD:D_SMA","C2480","3"
"D4","CHG","LED_SMD:LED_0805_2012Metric","C84256","1"
"J1","OLED","Connector_PinHeader_2.54mm:PinHeader_1x04_P2.54mm_Vertical","","1"
"J2","ENCODER","Connector_PinHeader_2.54mm:PinHeader_1x05_P2.54mm_Vertical","","1"
"J3","WS2812","Connector_PinHeader_2.54mm:PinHeader_1x03_P2.54mm_Vertical","","1"
"J4","HX711_MODULE","Connector_PinSocket_2.54mm:PinSocket_1x04_P2.54mm_Vertical","C2718488","1"
"J5","SDCARD","Connector_PinHeader_2.54mm:PinHeader_1x06_P2.54mm_Vertical","","1"
"J6","5V_IN","Connector_PinHeader_2.54mm:PinHeader_1x02_P2.54mm_Vertical","","1"
"J7","LIPO","Connector_JST:JST_PH_S2B-PH-K_1x02_P2.00mm_Horizontal","C173752","1"
"J8","PWR_SW","Connector_PinHeader_2.54mm:PinHeader_1x02_P2.54mm_Vertical","","1"
"J9","USB-C PD 12V","Connector_USB:USB_C_Receptacle_GCT_USB4125-xx-x_6P_TopMnt_Horizontal","C3151650","1"
"J10","MOTOR","Connector_PinHeader_2.54mm:PinHeader_1x04_P2.54mm_Vertical","","1"
"L1","10u","Inductor_SMD:L_Bourns_SRN6045TA","C2046332","1"
"Q2","AO3401A","Package_TO_SOT_SMD:SOT-23","C15127","1"
"R3","330","Resistor_SMD:R_0805_2012Metric","C17630","1"
"R4","2k","Resistor_SMD:R_0805_2012Metric","C17604","1"
"R5,R11","1k","Resistor_SMD:R_0805_2012Metric","C17513","2"
"R6","100k","Resistor_SMD:R_0805_2012Metric","C149504","1"
"R7","75k","Resistor_SMD:R_0805_2012Metric","C17819","1"
"R8,R13,R14","10k","Resistor_SMD:R_0805_2012Metric","C17414","3"
"R9,R10","220k","Resistor_SMD:R_0805_2012Metric","C17556","2"
"R12","24k","Resistor_SMD:R_0805_2012Metric","C17575","1"
"SW1","LEFT","Button_Switch_THT:SW_PUSH_6mm","C393938","1"
"SW2","RIGHT","Button_Switch_THT:SW_PUSH_6mm","C393938","1"
"U1","Pico 2 W","Module:RaspberryPi_Pico_Common_THT","","1"
"U3","MCP73831-2-OT","Package_TO_SOT_SMD:SOT-23-5","C424093","1"
"U4","MT3608","Package_TO_SOT_SMD:SOT-23-6","C84817","1"
"U5","CH224K","Package_SO:SSOP-10-1EP_3.9x4.9mm_P1mm_EP2.1x3.3mm","C970725","1"

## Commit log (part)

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2023-07-27 initial
2023-07-28 added wait and confirm instructions
2023-07-29 v1.0.0 rp2040 software
2023-07-29 first workinng api for gettings recipes
2023-07-29 proxy pass working for api
2023-07-31 added frontend pycharm project
2023-11-01 more WIP
2023-11-01 added calibration mode
2023-11-06 ui font breaking working
2023-11-06 a bit better
2023-11-07 scale working + tare
2023-11-07 good working
2023-11-08 licence modified
2023-11-11 static site
2023-12-21 Rename mixmeasurebuddy_v1.0.0 to mixmeasurebuddy__picow_v1.0.0
2023-12-21 Rename mixmeasurebuddy__picow_v1.0.0 to mixmeasurebuddy__picow_v1.0.0.u2f
2023-12-22 added first manifest try
2023-12-24 build micropython image with custom code working
2023-12-24 rework started
2023-12-24 more rework
2023-12-24 typo fix in build script
2023-12-24 added images
2023-12-25 added set font method
2023-12-25 added build folder
2023-12-25 added usage of example_recipes.py
2024-03-31 Update Dockerfile
2024-04-02 recipe link route
2024-04-09 chmod
2024-04-09 added npm shark for image
2024-04-09 frontend route apache working
2024-04-20 button management, settings, recipe update
2024-04-20 menu manager working
2024-04-21 menu working, submenus working
2024-04-21 leds and recipe menu entires working
2024-04-21 added micropyserver
2024-04-22 working on reworked recipe format
2024-04-22 more recipe logic stuff
2024-04-22 more recipe stuff
2024-04-22 starting recipe state handling
2024-04-22 more stuff
2024-04-24 added updated schematic
2024-04-25 archived firmware for 0.9.0 added
2024-04-25 added more build images
2024-04-25 working firmware v0.9.1
    fixed calibration plugin
2024-04-26 added documentation
2024-04-26 added submenu capabilities
    prepaeration for 1.0
    added drink multiplier
2024-04-27 fixed scale menu - v0.9.8
2024-04-27 added v0.9.8 build
2024-04-27 move more final libs into static modules
2024-04-29 added new stls
2024-04-29 fixed manual
2024-04-29 added new exported stls for v1.0.0
2024-05-03 fixed ring body
2024-05-03 another fixed ring body version
2024-05-03 Update Dockerfile, added break system packages flag
2024-05-03 new cellplates
2024-05-21 fixed encoder clamp
2024-07-16 added static recipe creation methods
2024-12-02 added rp pico 2350 support
2024-12-02 more example recipes
2024-12-03 added v1.1.0 to firmware archive
2025-10-25 Create Mojito recipe with ingredients and steps
    Added a recipe for Mojito including ingredients and steps.
2025-10-25 Create Whiskey Sour recipe
    Added a new recipe for Whiskey Sour with ingredients and steps.
2025-10-25 Create Negroni recipe with preparation steps
    Added a recipe for Negroni including ingredients and steps.
2025-10-25 Create Cosmopolitan recipe with ingredients and steps
    Added a recipe for Cosmopolitan cocktail with ingredients and steps.
2025-10-25 Create Mai Tai recipe file
    Added Mai Tai recipe with ingredients and steps.
2025-10-25 Add Old Fashioned cocktail recipe
    Added a recipe for the Old Fashioned cocktail with detailed steps and ingredients.
2025-10-25 Create Espresso Martini recipe
    Added recipe for Espresso Martini with ingredients and steps.
2025-10-25 Create Piña Colada recipe
    Added a recipe for Piña Colada including ingredients and steps.
2025-10-26 Rename Espresso_Martini.recip to Espresso_Martini.recipe
2025-10-26 more reciepes added
2025-10-26 reworked frontend to be a static site instead of using an api
2025-10-26 fix ?
2025-10-26 fix json recieps
2025-10-26 more recipes
2025-10-26 npm audit
2025-10-26 api route
2025-10-27 backend
2025-10-27 backend check
2025-10-27 api working
2025-10-28 reverse proxy api
2025-10-28 manage api working
